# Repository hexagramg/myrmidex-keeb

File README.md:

# myrmidex-keeb
Myrmidex is split ergo hotswappable keyboard with two rotary encoders. 
Supports controllers with Pro-Micro layout, has footprints for power switch and battery. 

In this repository you will find gerbers and schematics. Gerbers were exported with jlcpcb support in mind. Schematics were made in kicad. 

Right now qmk support is implemented, you can find it [here](https://github.com/hexagramg/qmk_firmware/tree/myrmidex/keyboards/myrmidex)

To build this keyboard you will need:
- SOD323 diodes of your choice x50
- PJ 320A trrs x2
- 0805 10k resistors x8
- 0805 10nf capacitors x4
- Kailh hotswap CPG151101S11 x48
- Alps ec11 encoders x2
- 48 mx compatible switches of your choice
- Pro-Micro x2
- Trrs cable

There are places for m2 standoffs, I used these:
- m2 4mm male-female standoff x16 (3mm is possible to fit) https://aliexpress.ru/item/4001271908929.html This one goes between pcb and bottom plate
- m2 3mm female-female standoff x16 https://aliexpress.ru/item/4001271908929.html This one between pcb and top plate
- m2 low profile screws x32 https://aliexpress.ru/item/32981714992.html Screw them tight on the bottom plate and somewhat loose on the top. 

Be careful on soldering left side, one diode on the bottom row is flipped. I will probably correct this in the next version, if there will be one.

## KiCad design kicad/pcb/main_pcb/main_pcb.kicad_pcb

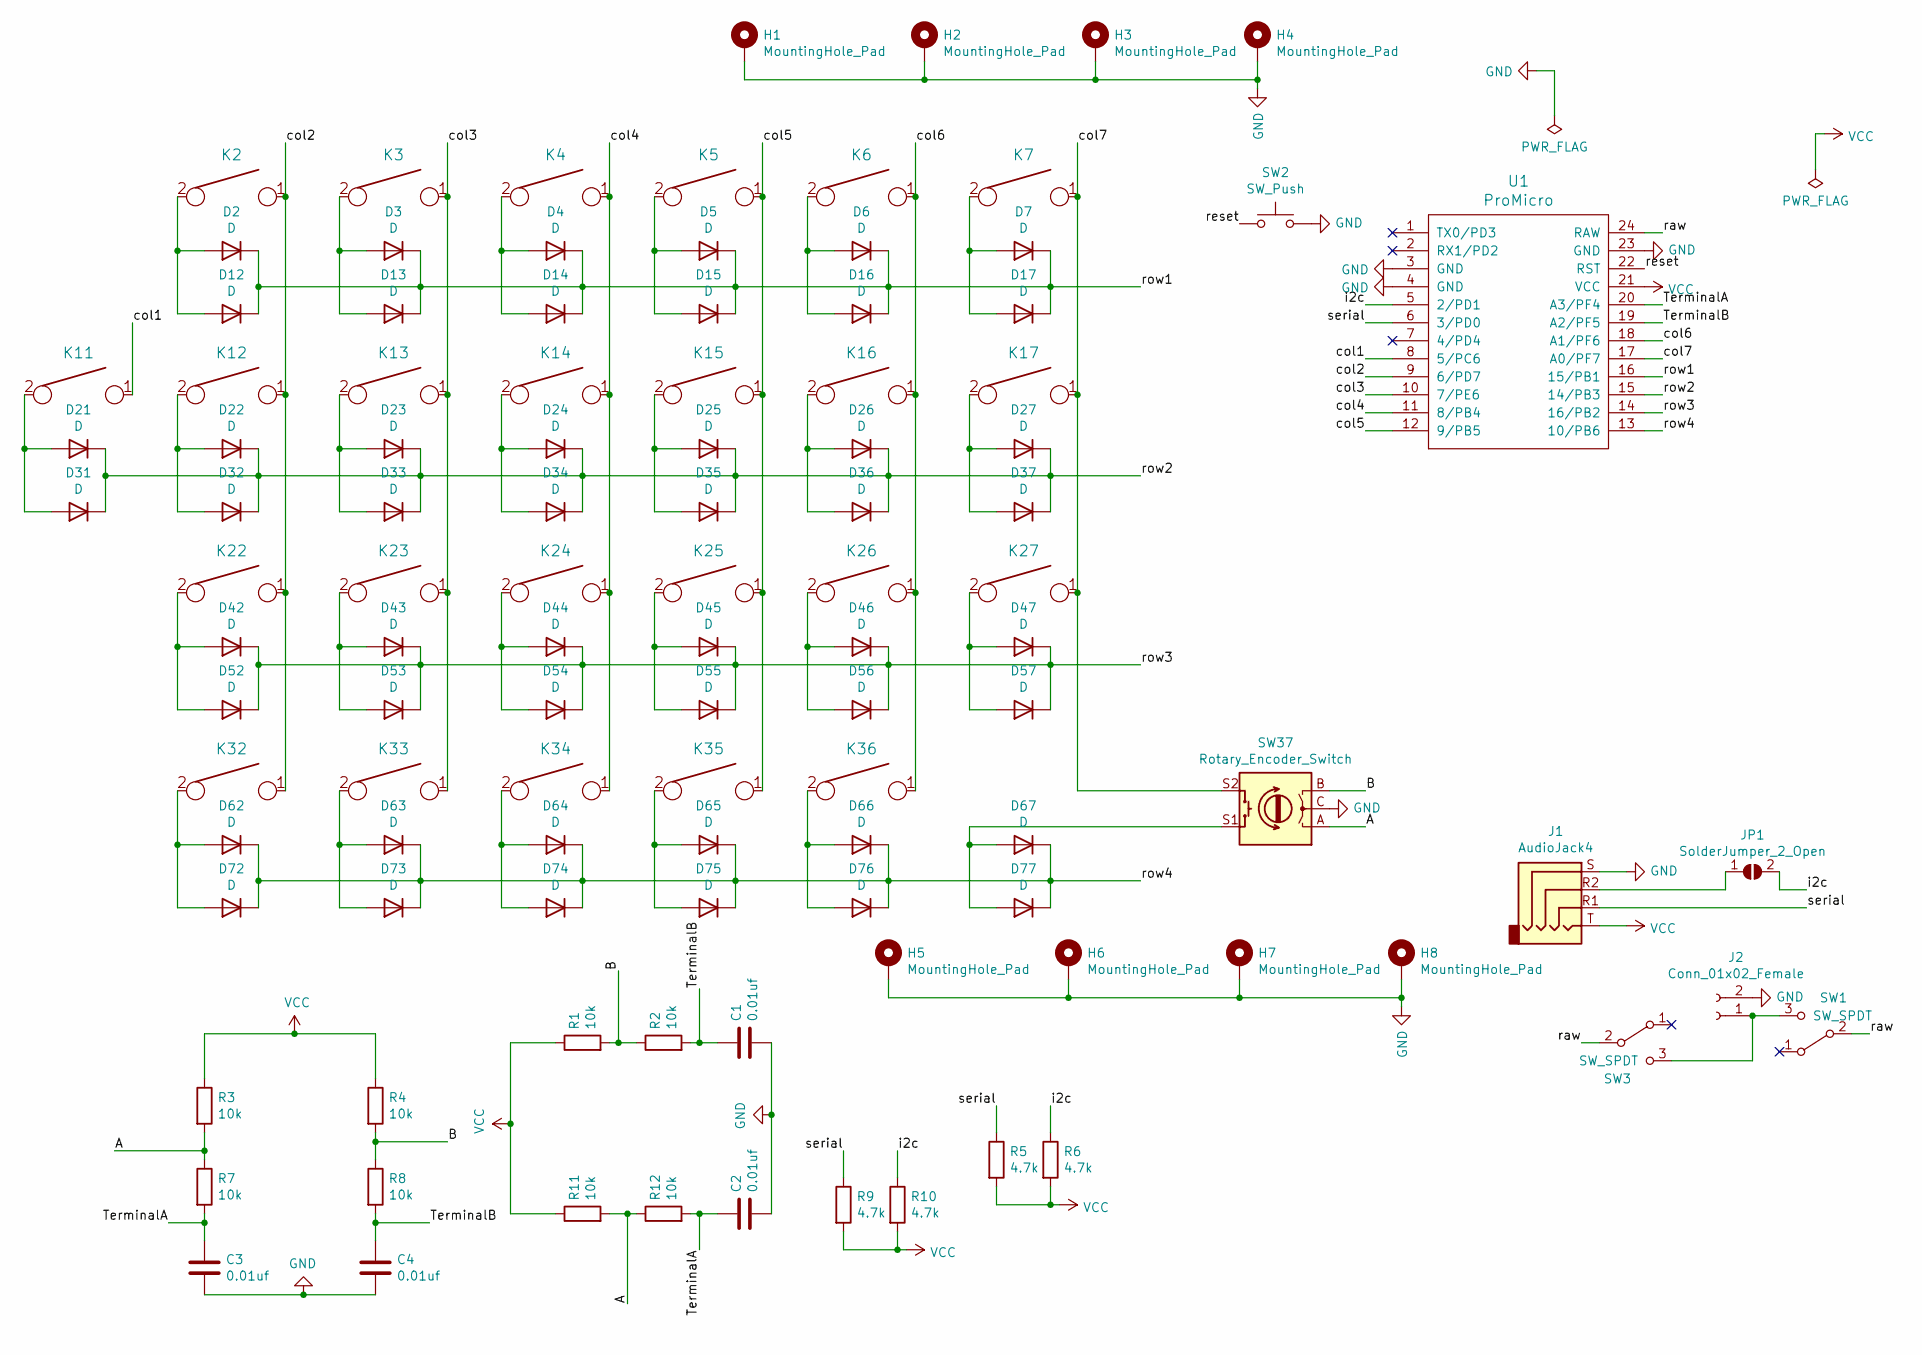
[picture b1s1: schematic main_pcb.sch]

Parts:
C1, C2, C3, C4: 0.01uf; C_0805_2012Metric_Pad1.18x1.45mm_HandSolder
D2, D3, D4, D5, D6, D7, D12, D13, D14, D15, D16, D17, D21, D22, D23, D24, D25, D26, D27, D31, D32, D33, D34, D35, D36, D37, D42, D43, D44, D45, D46, D47, D52, D53, D54, D55, D56, D57, D62, D63, D64, D65, D66, D67, D72, D73, D74, D75, D76, D77: D; D_0805_2012Metric_Pad1.15x1.40mm_HandSolder
H1, H2, H3, H4, H5, H6, H7, H8: MountingHole_Pad; MountingHole_2.2mm_M2_ISO14580_Pad
J1: AudioJack4; TRRS_PJ-320A_double
J2: Conn_01x02_Female; PinSocket_1x02_P2.54mm_Vertical
JP1: SolderJumper_2_Open; SolderJumper-2_P1.3mm_Open_Pad1.0x1.5mm
K2, K3, K4, K5, K6, K7, K11, K12, K13, K14, K15, K16, K17, K22, K23, K24, K25, K26, K27, K32, K33, K34, K35, K36: KEYSW-keyboard_parts; Kailh_socket_MX_optional_reversible_with_holes
R1, R2, R3, R4, R7, R8, R11, R12: 10k; R_0805_2012Metric_Pad1.20x1.40mm_HandSolder
R5, R6, R9, R10: 4.7k; R_0805_2012Metric_Pad1.20x1.40mm_HandSolder
SW1, SW3: SW_SPDT; SW_SPDT+H-MSK12C01_hor(7pin_SMD)
SW2: SW_Push; Switch_Reset_THT
SW37: Rotary_Encoder_Switch; RotaryEncoder_Alps_EC11E-Switch_Vertical_H20mm
U1: ProMicro; ProMicro_Dual

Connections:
/A: R3.2, R7.1, R11.2, R12.1, SW37.A
/B: R1.2, R2.1, R4.2, R8.1, SW37.B
/TerminalA: C2.1, C3.1, R7.2, R12.2, U1.20 (A3/PF4)
/TerminalB: C1.1, C4.1, R2.2, R8.2, U1.19 (A2/PF5)
/col1: K11.1, U1.8 (5/PC6)
/col2: K2.1, K12.1, K22.1, K32.1, U1.9 (6/PD7)
/col3: K3.1, K13.1, K23.1, K33.1, U1.10 (7/PE6)
/col4: K4.1, K14.1, K24.1, K34.1, U1.11 (8/PB4)
/col5: K5.1, K15.1, K25.1, K35.1, U1.12 (9/PB5)
/col6: K6.1, K16.1, K26.1, K36.1, U1.18 (A1/PF6)
/col7: K7.1, K17.1, K27.1, SW37.S2, U1.17 (A0/PF7)
/i2c: JP1.2 (B), R6.1, R10.1, U1.5 (2/PD1)
/raw: SW1.2 (B), SW3.2 (B), U1.24 (RAW)
/reset: SW2.1, U1.22 (RST)
/row1: D2.1 (K), D3.1 (K), D4.1 (K), D5.1 (K), D6.1 (K), D7.1 (K), D12.1 (K), D13.1 (K), D14.1 (K), D15.1 (K), D16.1 (K), D17.1 (K), U1.16 (15/PB1)
/row2: D21.1 (K), D22.1 (K), D23.1 (K), D24.1 (K), D25.1 (K), D26.1 (K), D27.1 (K), D31.1 (K), D32.1 (K), D33.1 (K), D34.1 (K), D35.1 (K), D36.1 (K), D37.1 (K), U1.15 (14/PB3)
/row3: D42.1 (K), D43.1 (K), D44.1 (K), D45.1 (K), D46.1 (K), D47.1 (K), D52.1 (K), D53.1 (K), D54.1 (K), D55.1 (K), D56.1 (K), D57.1 (K), U1.14 (16/PB2)
/row4: D62.1 (K), D63.1 (K), D64.1 (K), D65.1 (K), D66.1 (K), D67.1 (K), D72.1 (K), D73.1 (K), D74.1 (K), D75.1 (K), D76.1 (K), D77.1 (K), U1.13 (10/PB6)
/serial: J1.R1, R5.1, R9.1, U1.6 (3/PD0)
GND: C1.2, C2.2, C3.2, C4.2, H1.1, H2.1, H3.1, H4.1, H5.1, H6.1, H7.1, H8.1, J1.S, J2.2, SW2.2, SW37.C, U1.3 (GND), U1.4 (GND), U1.23 (GND)
unnamed: D2.2 (A), D12.2 (A), K2.2
unnamed: D3.2 (A), D13.2 (A), K3.2
unnamed: D4.2 (A), D14.2 (A), K4.2
unnamed: D5.2 (A), D15.2 (A), K5.2
unnamed: D6.2 (A), D16.2 (A), K6.2
unnamed: D7.2 (A), D17.2 (A), K7.2
unnamed: D21.2 (A), D31.2 (A), K11.2
unnamed: D22.2 (A), D32.2 (A), K12.2
unnamed: D23.2 (A), D33.2 (A), K13.2
unnamed: D24.2 (A), D34.2 (A), K14.2
unnamed: D25.2 (A), D35.2 (A), K15.2
unnamed: D26.2 (A), D36.2 (A), K16.2
unnamed: D27.2 (A), D37.2 (A), K17.2
unnamed: D42.2 (A), D52.2 (A), K22.2
unnamed: D43.2 (A), D53.2 (A), K23.2
unnamed: D44.2 (A), D54.2 (A), K24.2
unnamed: D45.2 (A), D55.2 (A), K25.2
unnamed: D46.2 (A), D56.2 (A), K26.2
unnamed: D47.2 (A), D57.2 (A), K27.2
unnamed: D62.2 (A), D72.2 (A), K32.2
unnamed: D63.2 (A), D73.2 (A), K33.2
unnamed: D64.2 (A), D74.2 (A), K34.2
unnamed: D65.2 (A), D75.2 (A), K35.2
unnamed: D66.2 (A), D76.2 (A), K36.2
unnamed: D67.2 (A), D77.2 (A), SW37.S1
unnamed: J1.R2, JP1.1 (A)
unnamed: J2.1, SW1.3 (C), SW3.3 (C)
VCC: J1.T, R1.1, R3.1, R4.1, R5.2, R6.2, R9.2, R10.2, R11.1, U1.21 (VCC)

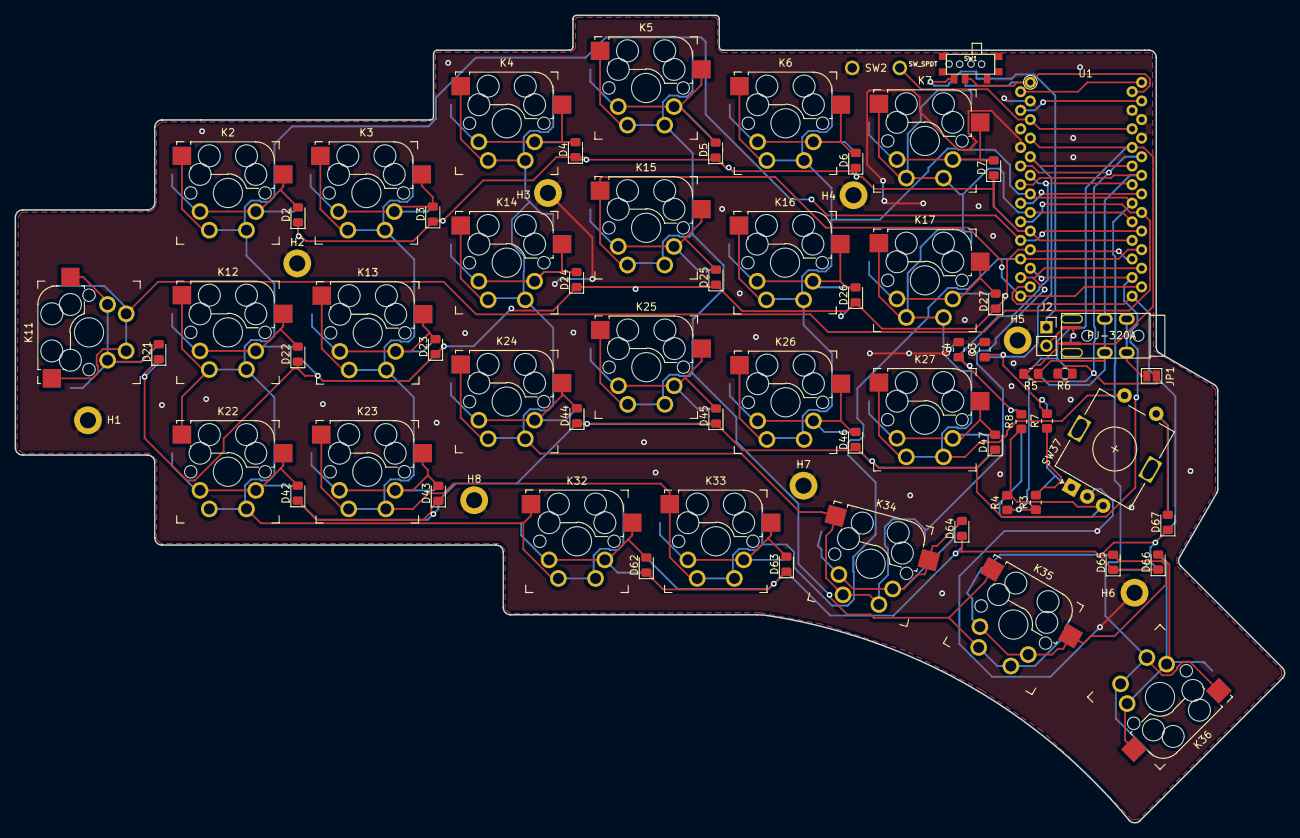
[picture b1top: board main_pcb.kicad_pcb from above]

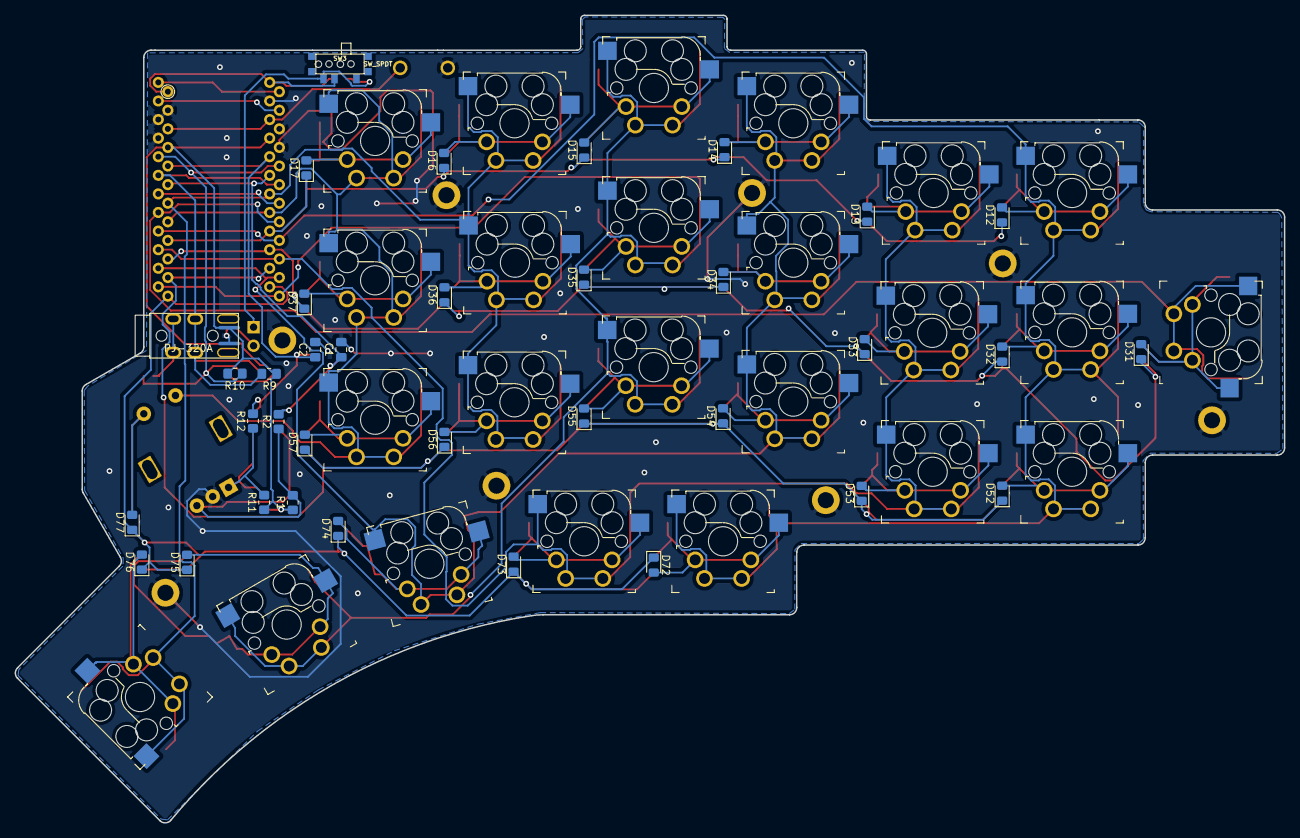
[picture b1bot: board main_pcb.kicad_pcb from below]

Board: 2 copper layers, 173.5 x 110.4 mm, 106 parts (34 on the bottom side), 48 nets.

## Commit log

2021-10-15 Sketches for all the future planes
2021-10-16 Main pcb done
2021-10-25 gerbers added
